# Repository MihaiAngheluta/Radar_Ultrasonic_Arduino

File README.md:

Radar Ultrasonic using Arduino Platform

For this project i used the following components:

- Arduino Nano;
- Stepper motor;
- Sensor Hall Module;
- Display LCD 16x2;
- Ultrasonic Sensor HC-SR04;
- Buzzer;
- Neodim Magnet;
- Bluetooth Module;

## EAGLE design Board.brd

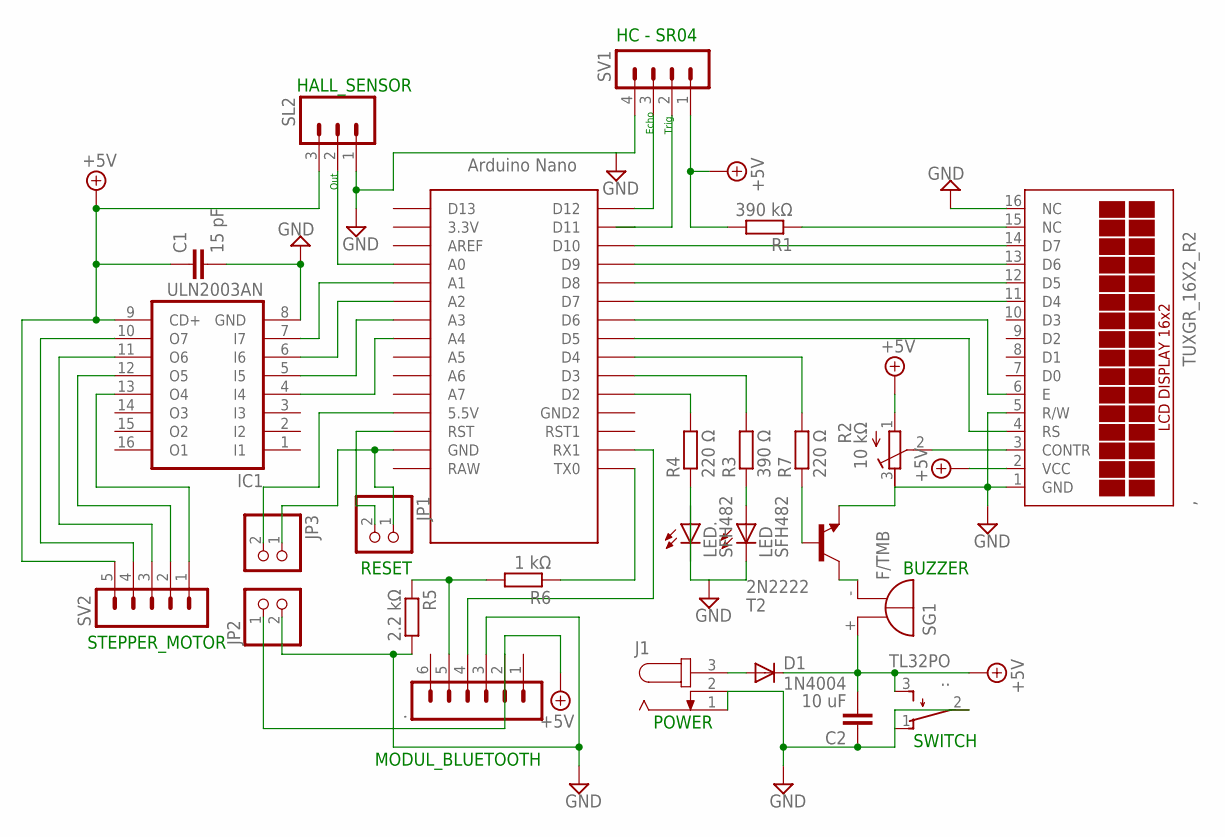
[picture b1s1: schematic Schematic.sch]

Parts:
,: TUXGR_16X2_R2
.: MA06-1
..: TL32PO; TL3XPO
C1: 15 pF; C025-024X044
C2: 10 uF; C025-024X044
D1: 1N4004; DO41-10
IC1: ULN2003AN; DIL16
J1: JACK-PLUG0; SPC4077
JP1, JP2, JP3: PINHD-1X2; 1X02
LED, LED.: SFH482
R1: 390 kΩ; 0207/10
R2: 10 kΩ; RTRIM3339P
R3: 390 Ω; 0207/10
R4, R7: 220 Ω; 0207/10
R5: 2.2 kΩ; 0207/10
R6: 1 kΩ; 0207/10
SG1: F/TMB
SL2: MA03; 03P
SV1: MA04-1
SV2: MA05-1
T2: 2N2222; TO92-EBC-OVAL
U$2: NANO

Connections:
+5V: ,.2 (VCC), ..2, ...3 (S), C1.1, C2.2, D1.C, IC1.9 (CD+), JP2.1, R1.2, R2.1 (E), SG1.+, SL2.3, SV1.1, SV2.5
GND: ,.1 (GND), ,.5 (R/W), ,.16 (NC), ..3, ...1 (O), ...2, C1.2, C2.1, IC1.8 (GND), J1.1, J1.2, JP2.2, LED.K (C), LED..A, LED..K (C), R2.3 (A), R4.1, R5.2, SL2.1, SV1.4, T2.E
unnamed: ,.3 (CONTR), R2.2 (S)
unnamed: ,.15 (NC), R1.1
unnamed: R4.2, U$2.D2
unnamed: R3.2, U$2.D3
unnamed: LED.A, R3.1
unnamed: R7.2, U$2.D4
unnamed: R7.1, T2.B
unnamed: IC1.7 (I7), U$2.A1
unnamed: IC1.6 (I6), U$2.A2
unnamed: ,.14 (D7), U$2.D10
unnamed: ,.13 (D6), U$2.D9
unnamed: SV1.2, U$2.D11
unnamed: SV1.3, U$2.D12
unnamed: IC1.5 (I5), U$2.A3
unnamed: IC1.4 (I4), U$2.A4
unnamed: ,.12 (D5), U$2.D8
unnamed: IC1.13 (O4), SV2.1
unnamed: IC1.12 (O5), SV2.2
unnamed: IC1.11 (O6), SV2.3
unnamed: IC1.10 (O7), SV2.4
unnamed: JP1.1, JP3.1, U$2.GND
unnamed: ,.11 (D4), U$2.D7
unnamed: JP1.2, U$2.RST
unnamed: SG1.-, T2.C
unnamed: ,.6 (E), U$2.D6
unnamed: SL2.2, U$2.A0
unnamed: ,.4 (RS), U$2.D5
unnamed: R6.1, U$2.TX0
unnamed: ..5, R5.1, R6.2
unnamed: ..4, U$2.RX1
unnamed: JP3.2, U$2.5V (5.5V)
unnamed: D1.A, J1.3

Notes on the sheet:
HALL_SENSOR
HC - SR04
STEPPER_MOTOR
MODUL_BLUETOOTH
SWITCH
POWER
RESET
BUZZER
Trig
Echo
Out

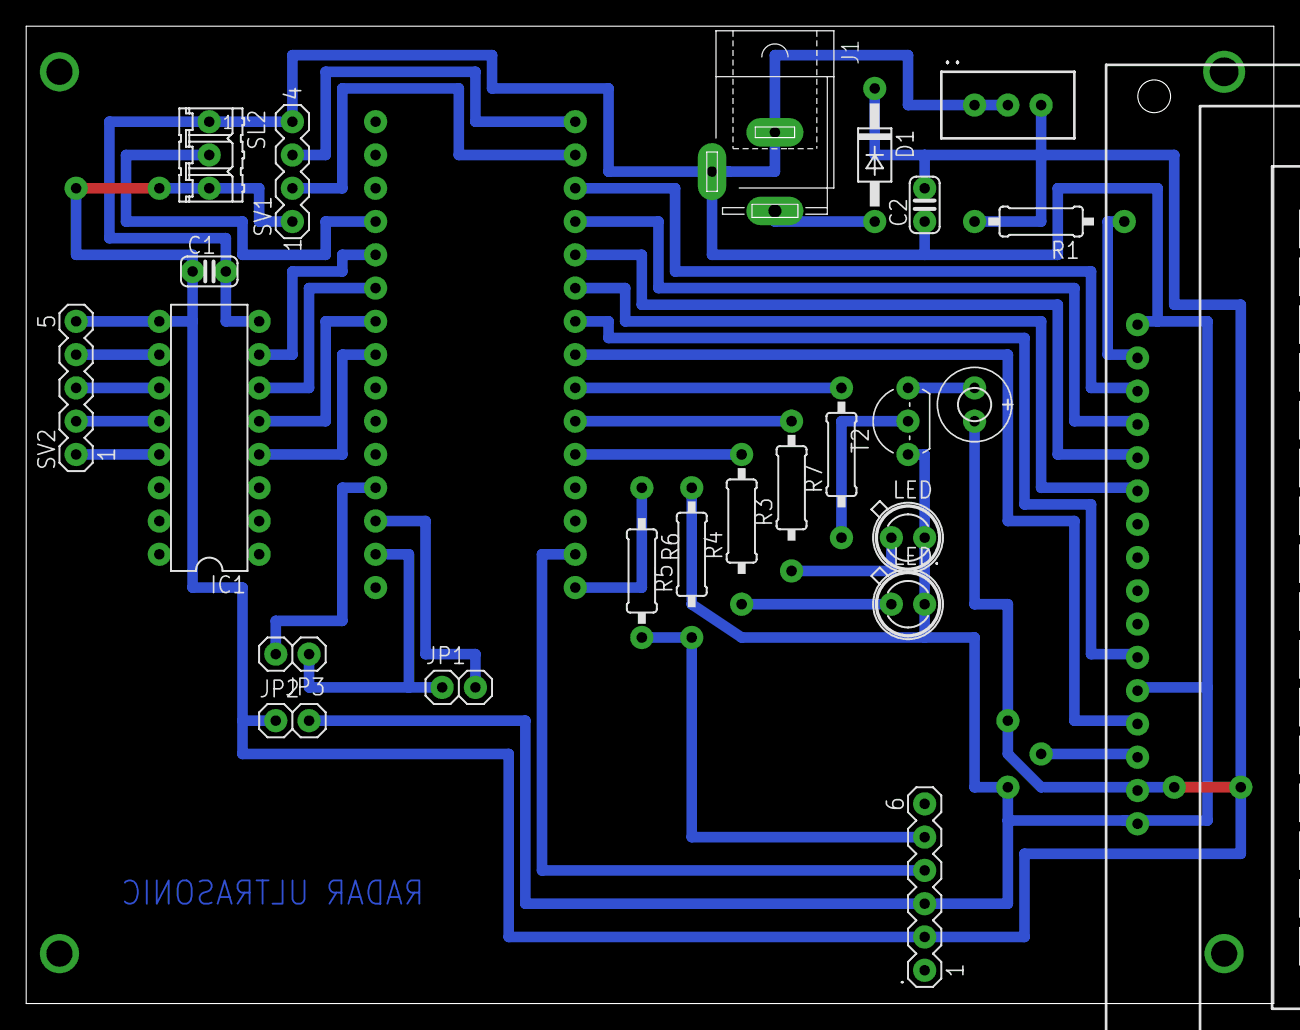
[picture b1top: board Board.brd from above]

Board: 2 copper layers, 95.2 x 74.6 mm, 26 parts (1 on the bottom side), 34 nets.

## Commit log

2019-02-26 Board pdf for print
2019-02-26 Graphic interface modified for radar for 0-360 degrees
2019-02-26 Software used for the graphic interface
2019-02-26 Add readme file
